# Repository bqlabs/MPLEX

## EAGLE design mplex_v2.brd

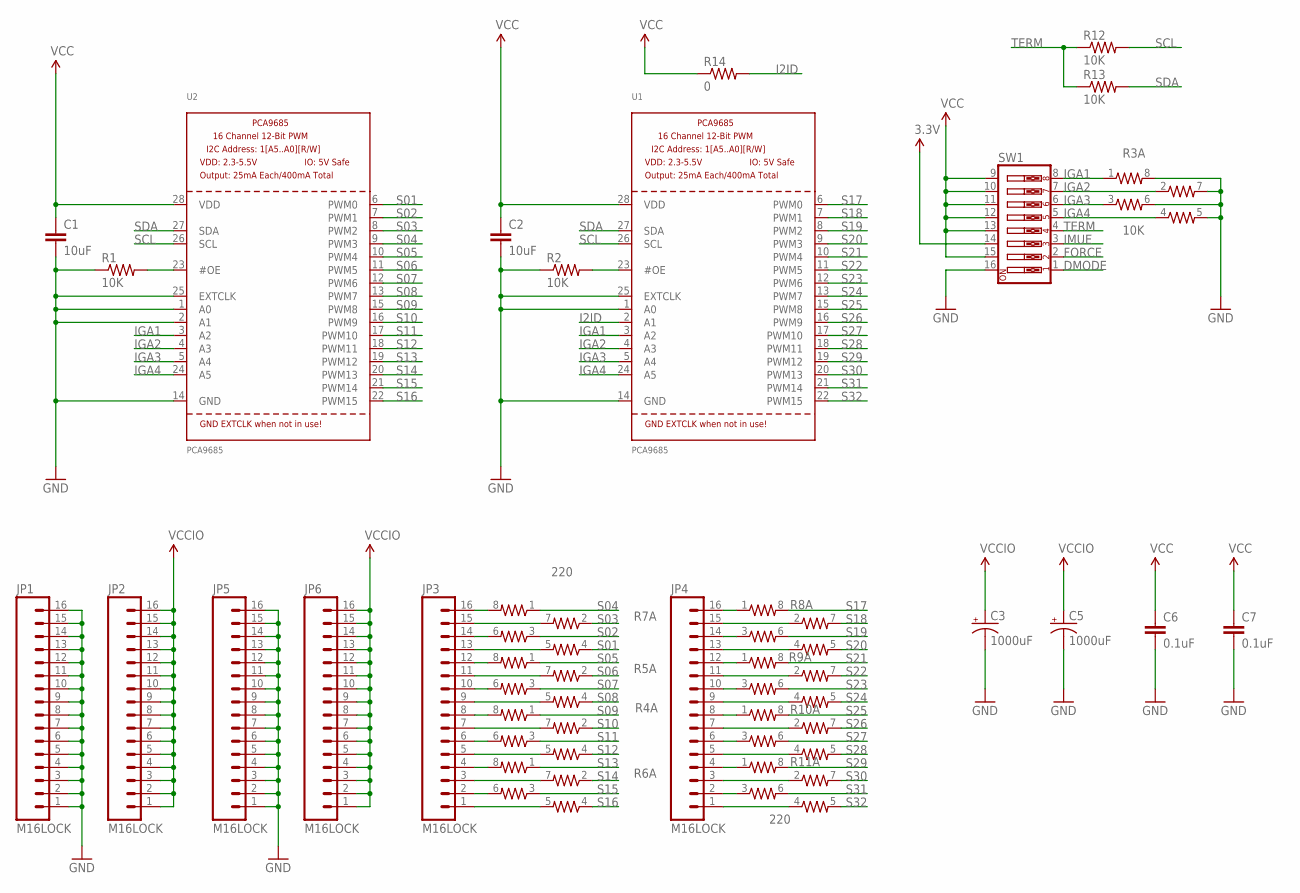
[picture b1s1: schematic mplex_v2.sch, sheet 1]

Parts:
C1, C2: 10uF; 0603-CAP
C3, C5: 1000uF; PANASONIC_D
C6, C7: 0.1uF; 0603-CAP
JP1, JP2, JP3, JP4, JP5, JP6: M16LOCK; 1X16_LOCK
R1, R2, R12, R13: 10K; 0603-RES
R3: 10K; 0603-ARV
R4, R5, R6, R7, R8, R9, R10, R11: 220; 0603-ARV
R14: 0; 0603-RES
SW1: SW_DIP-8-SMT-HALFSIZE; DIPSWITCH-08-50MIL
U1, U2: PCA9685; TSSOP28

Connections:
3.3V: SW1.14; also elsewhere on the board
DMODE: SW1.1; also elsewhere on the board
FORCE: SW1.2; also elsewhere on the board
GND: C1.2, C2.2, C3.-, C5.-, C6.2, C7.2, JP1.1, JP1.2, JP1.3, JP1.4, JP1.5, JP1.6, JP1.7, JP1.8, JP1.9, JP1.10, JP1.11, JP1.12, JP1.13, JP1.14, JP1.15, JP1.16, JP5.1, JP5.2, JP5.3, JP5.4, JP5.5, JP5.6, JP5.7, JP5.8, JP5.9, JP5.10, JP5.11, JP5.12, JP5.13, JP5.14, JP5.15, JP5.16, R1.1, R2.1, R3.5 (2), R3.6 (2), R3.7 (2), R3.8 (2), SW1.16, U1.1 (A0), U1.14 (GND), U1.25 (EXTCLK), U2.1 (A0), U2.2 (A1), U2.14 (GND), U2.25 (EXTCLK); also elsewhere on the board
I2ID: R14.2, U1.2 (A1)
IGA1: R3.1, SW1.8, U1.3 (A2), U2.3 (A2); also elsewhere on the board
IGA2: R3.2 (1), SW1.7, U1.4 (A3), U2.4 (A3); also elsewhere on the board
IGA3: R3.3 (1), SW1.6, U1.5 (A4), U2.5 (A4); also elsewhere on the board
IGA4: R3.4 (1), SW1.5, U1.24 (A5), U2.24 (A5); also elsewhere on the board
IMUE: SW1.3; also elsewhere on the board
unnamed: JP3.16, R7.8 (2)
unnamed: JP3.15, R7.7 (2)
unnamed: R1.2, U2.23 (#OE)
unnamed: R2.2, U1.23 (#OE)
unnamed: JP3.14, R7.6 (2)
unnamed: JP3.13, R7.5 (2)
unnamed: JP3.11, R5.7 (2)
unnamed: JP3.12, R5.8 (2)
unnamed: JP3.10, R5.6 (2)
unnamed: JP3.9, R5.5 (2)
unnamed: JP3.8, R4.8 (2)
unnamed: JP3.7, R4.7 (2)
unnamed: JP3.6, R4.6 (2)
unnamed: JP3.5, R4.5 (2)
unnamed: JP3.4, R6.8 (2)
unnamed: JP3.3, R6.7 (2)
unnamed: JP3.2, R6.6 (2)
unnamed: JP3.1, R6.5 (2)
unnamed: JP4.16, R8.1
unnamed: JP4.15, R8.2 (1)
unnamed: JP4.14, R8.3 (1)
unnamed: JP4.13, R8.4 (1)
unnamed: JP4.12, R9.1
unnamed: JP4.11, R9.2 (1)
unnamed: JP4.10, R9.3 (1)
unnamed: JP4.9, R9.4 (1)
unnamed: JP4.8, R10.1
unnamed: JP4.7, R10.2 (1)
unnamed: JP4.6, R10.3 (1)
unnamed: JP4.5, R10.4 (1)
unnamed: JP4.4, R11.1
unnamed: JP4.3, R11.2 (1)
unnamed: JP4.2, R11.3 (1)
unnamed: JP4.1, R11.4 (1)
S01: R7.4 (1), U2.6 (PWM0)
S02: R7.3 (1), U2.7 (PWM1)
S03: R7.2 (1), U2.8 (PWM2)
S04: R7.1, U2.9 (PWM3)
S05: R5.1, U2.10 (PWM4)
S06: R5.2 (1), U2.11 (PWM5)
S07: R5.3 (1), U2.12 (PWM6)
S08: R5.4 (1), U2.13 (PWM7)
S09: R4.1, U2.15 (PWM8)
S10: R4.2 (1), U2.16 (PWM9)
S11: R4.3 (1), U2.17 (PWM10)
S12: R4.4 (1), U2.18 (PWM11)
S13: R6.1, U2.19 (PWM12)
S14: R6.2 (1), U2.20 (PWM13)
S15: R6.3 (1), U2.21 (PWM14)
S16: R6.4 (1), U2.22 (PWM15)
S17: R8.8 (2), U1.6 (PWM0)
S18: R8.7 (2), U1.7 (PWM1)
S19: R8.6 (2), U1.8 (PWM2)
S20: R8.5 (2), U1.9 (PWM3)
S21: R9.8 (2), U1.10 (PWM4)
S22: R9.7 (2), U1.11 (PWM5)
S23: R9.6 (2), U1.12 (PWM6)
S24: R9.5 (2), U1.13 (PWM7)
S25: R10.8 (2), U1.15 (PWM8)
S26: R10.7 (2), U1.16 (PWM9)
S27: R10.6 (2), U1.17 (PWM10)
S28: R10.5 (2), U1.18 (PWM11)
S29: R11.8 (2), U1.19 (PWM12)
S30: R11.7 (2), U1.20 (PWM13)
S31: R11.6 (2), U1.21 (PWM14)
S32: R11.5 (2), U1.22 (PWM15)
SCL: R12.2, U1.26 (SCL), U2.26 (SCL); also elsewhere on the board
SDA: R13.2, U1.27 (SDA), U2.27 (SDA); also elsewhere on the board
TERM: R12.1, R13.1, SW1.4
VCC: C1.1, C2.1, C6.1, C7.1, R14.1, SW1.9, SW1.10, SW1.11, SW1.12, SW1.13, SW1.15, U1.28 (VDD), U2.28 (VDD); also elsewhere on the board
VCCIO: C3.+, C5.+, JP2.1, JP2.2, JP2.3, JP2.4, JP2.5, JP2.6, JP2.7, JP2.8, JP2.9, JP2.10, JP2.11, JP2.12, JP2.13, JP2.14, JP2.15, JP2.16, JP6.1, JP6.2, JP6.3, JP6.4, JP6.5, JP6.6, JP6.7, JP6.8, JP6.9, JP6.10, JP6.11, JP6.12, JP6.13, JP6.14, JP6.15, JP6.16; also elsewhere on the board

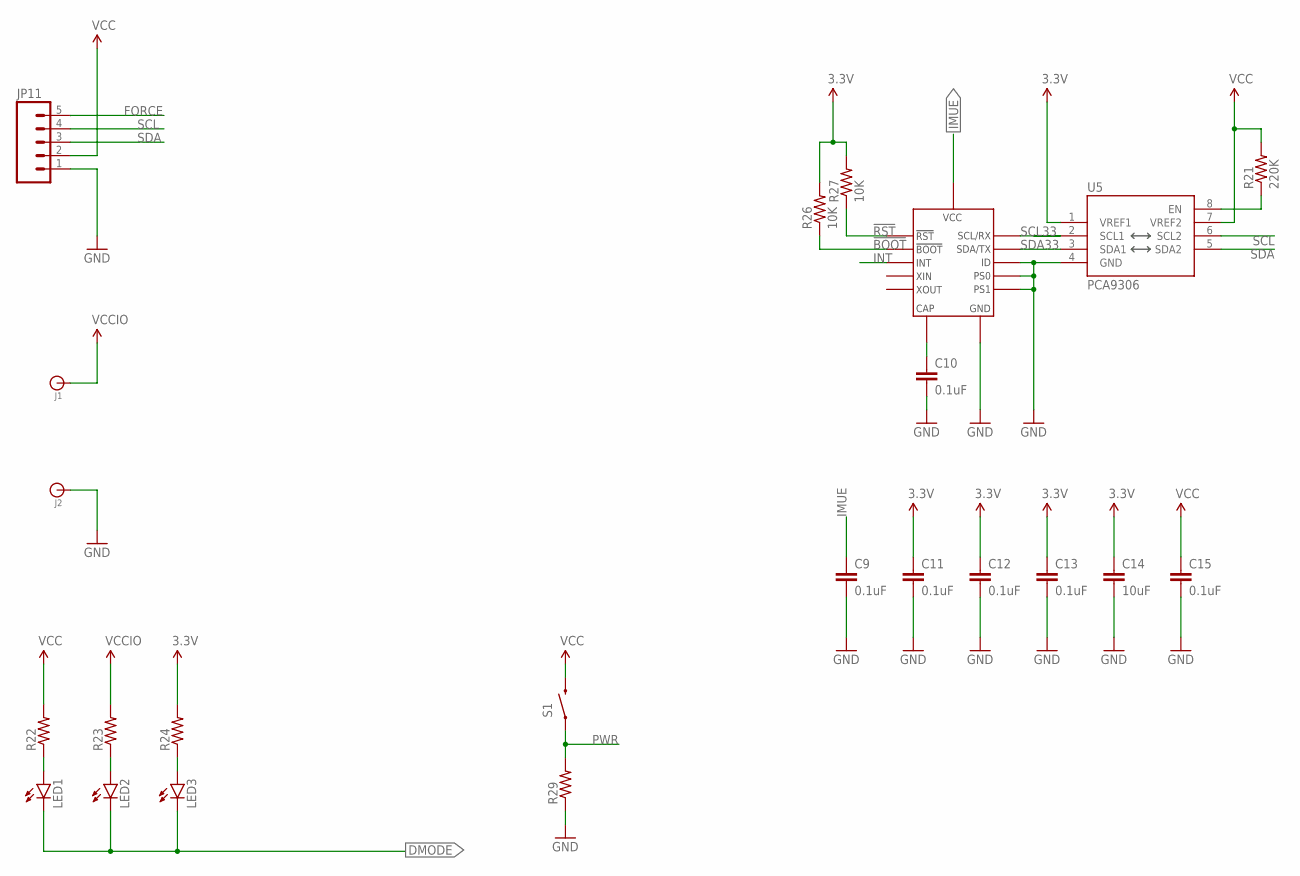
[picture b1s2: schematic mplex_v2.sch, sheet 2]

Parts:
C9, C10, C11, C12, C13, C15: 0.1uF; 0603-CAP
C14: 10uF; 0603-CAP
J1, J2: BANANA_CONN
JP11: M05LOCK; 1X05_LOCK
LED1, LED2, LED3: LED0603; LED-0603
R21: 220K; 0603-RES
R22, R23, R24, R29: RESISTOR0603-RES; 0603-RES
R26, R27: 10K; 0603-RES
S1: SWITCH-MOMENTARY-2SMD; TACTILE-SWITCH-SMD
U4: BNO055
U5: PCA9306; PCA9306DC-1:1

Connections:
3.3V: C11.1, C12.1, C13.1, C14.1, R24.2, R26.2, R27.2, U5.1 (VREF1); also elsewhere on the board
!BOOT: R26.1, U4.4 (BOOT)
!RST: R27.1, U4.1 (RST)
DMODE: LED1.C, LED2.C, LED3.C; also elsewhere on the board
FORCE: JP11.5; also elsewhere on the board
GND: C9.2, C10.2, C11.2, C12.2, C13.2, C14.2, C15.2, J2.P$1, JP11.1, R29.1, U4.2 (GND), U4.5 (PS1), U4.6 (PS0), U4.10 (GND), U4.15 (GND), U4.16 (GND), U4.17 (ID), U4.18 (GND), U4.25 (GND), U5.4 (GND); also elsewhere on the board
IMUE: C9.1, U4.3 (VCC), U4.28 (VCC); also elsewhere on the board
INT: U4.14 (INT)
unnamed: LED1.A, R22.1
unnamed: R21.1, U5.8 (EN)
unnamed: LED2.A, R23.1
unnamed: C10.1, U4.9 (CAP)
unnamed: LED3.A, R24.1
PWR: R29.2, S1.1
SCL: JP11.4, U5.6 (SCL2); also elsewhere on the board
SCL33: U4.19 (SCL/RX), U5.2 (SCL1)
SDA: JP11.3, U5.5 (SDA2); also elsewhere on the board
SDA33: U4.20 (SDA/TX), U5.3 (SDA1)
VCC: C15.1, JP11.2, R21.2, R22.2, S1.3 (2), U5.7 (VREF2); also elsewhere on the board
VCCIO: J1.P$1, R23.2; also elsewhere on the board

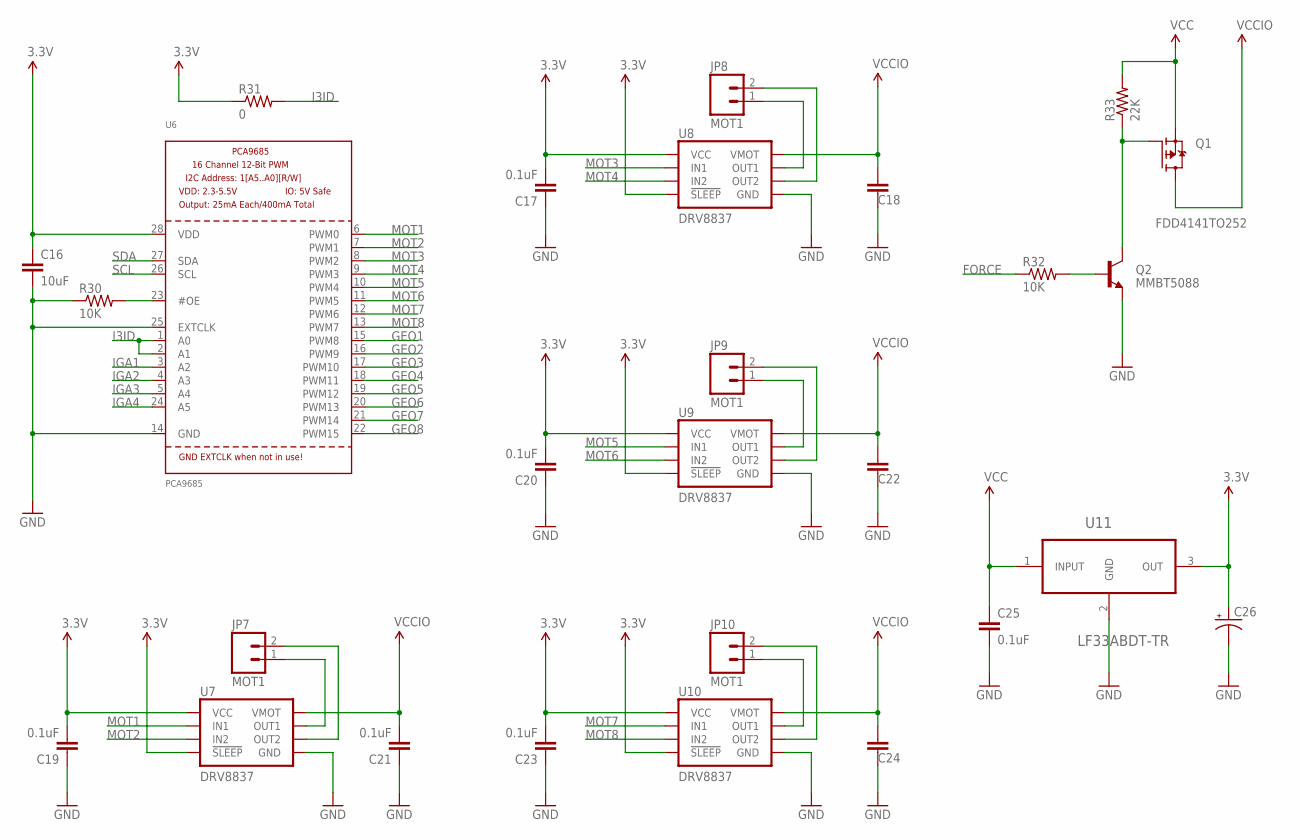
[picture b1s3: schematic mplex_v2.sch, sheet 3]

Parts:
C16: 10uF; 0603-CAP
C17, C18, C19, C20, C21, C22, C23, C24: 0.1uF; 0603-CAP
C25: 0.1uF; 1210
C26: CAP_POLD; PANASONIC_D
JP7, JP8, JP9, JP10: MOT1; MOLEX-1X2
Q1: FDD4141TO252; TO252
Q2: MMBT5088; SOT23-3
R30, R32: 10K; 0603-RES
R31: 0; 0603-RES
R33: 22K; 0603-RES
U6: PCA9685; TSSOP28
U7, U8, U9, U10: DRV8837; DSG
U11: LF33ABDT-TR; TO228P972X240-3N

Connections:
3.3V: C16.1, C17.2, C19.2, C20.2, C23.2, C26.+, R31.1, U6.28 (VDD), U7.7 (!SLEEP), U7.8 (VCC), U8.7 (!SLEEP), U8.8 (VCC), U9.7 (!SLEEP), U9.8 (VCC), U10.7 (!SLEEP), U10.8 (VCC), U11.3 (OUT); also elsewhere on the board
FORCE: R32.1; also elsewhere on the board
GEO1: U6.15 (PWM8)
GEO2: U6.16 (PWM9)
GEO3: U6.17 (PWM10)
GEO4: U6.18 (PWM11)
GEO5: U6.19 (PWM12)
GEO6: U6.20 (PWM13)
GEO7: U6.21 (PWM14)
GEO8: U6.22 (PWM15)
GND: C16.2, C17.1, C18.1, C19.1, C20.1, C21.1, C22.1, C23.1, C24.1, C25.2, C26.-, Q2.2 (E), R30.1, U6.14 (GND), U6.25 (EXTCLK), U7.4 (GND), U7.PAD (GND), U8.4 (GND), U8.PAD (GND), U9.4 (GND), U9.PAD (GND), U10.4 (GND), U10.PAD (GND), U11.2 (GND); also elsewhere on the board
I3ID: R31.2, U6.1 (A0), U6.2 (A1)
IGA1: U6.3 (A2); also elsewhere on the board
IGA2: U6.4 (A3); also elsewhere on the board
IGA3: U6.5 (A4); also elsewhere on the board
IGA4: U6.24 (A5); also elsewhere on the board
MOT1: U6.6 (PWM0), U7.6 (IN1)
MOT2: U6.7 (PWM1), U7.5 (IN2)
MOT3: U6.8 (PWM2), U8.6 (IN1)
MOT4: U6.9 (PWM3), U8.5 (IN2)
MOT5: U6.10 (PWM4), U9.6 (IN1)
MOT6: U6.11 (PWM5), U9.5 (IN2)
MOT7: U6.12 (PWM6), U10.6 (IN1)
MOT8: U6.13 (PWM7), U10.5 (IN2)
unnamed: R30.2, U6.23 (#OE)
unnamed: JP7.1, U7.2 (OUT1)
unnamed: JP7.2, U7.3 (OUT2)
unnamed: JP8.1, U8.2 (OUT1)
unnamed: JP8.2, U8.3 (OUT2)
unnamed: JP9.1, U9.2 (OUT1)
unnamed: JP9.2, U9.3 (OUT2)
unnamed: JP10.1, U10.2 (OUT1)
unnamed: Q2.1 (B), R32.2
unnamed: Q1.1 (G), Q2.3 (C), R33.1
unnamed: JP10.2, U10.3 (OUT2)
SCL: U6.26 (SCL); also elsewhere on the board
SDA: U6.27 (SDA); also elsewhere on the board
VCC: C25.1, Q1.2 (S), R33.2, U11.1 (INPUT); also elsewhere on the board
VCCIO: C18.2, C21.2, C22.2, C24.2, Q1.3 (D), U7.1 (VMOT), U8.1 (VMOT), U9.1 (VMOT), U10.1 (VMOT); also elsewhere on the board

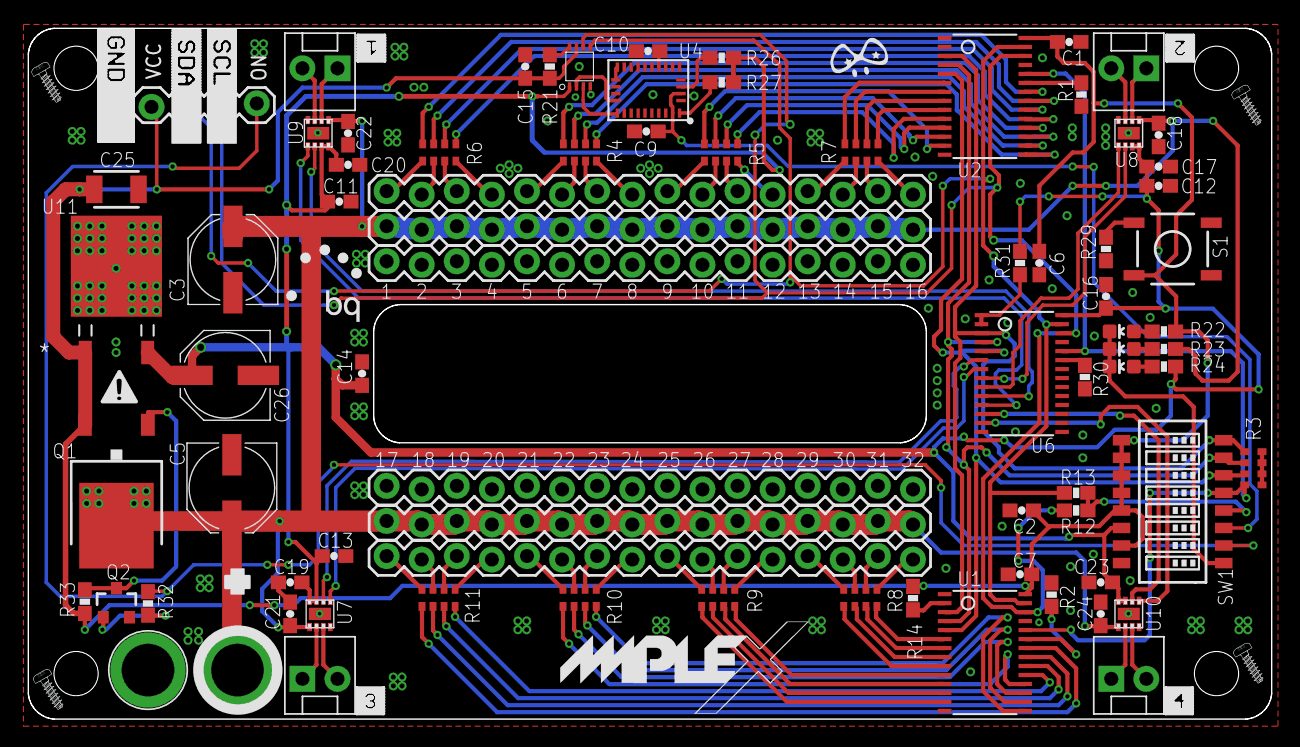
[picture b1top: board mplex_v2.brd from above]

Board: 2 copper layers, 90.0 x 50.0 mm, 94 parts (0 on the bottom side), 111 nets.

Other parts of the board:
U$1, U$3, U$4, U$6: SCREW
U$2: MPLEX_LOGO
U$5: S_1
U$7: S_ATTENTION
U$8: PIGHIXXX_LOGO
U$9: BQ_LOGO_SMALL
U$10: S_2
U$11: S_3
U$12: S_4
U$13: S_SCL
U$14: S_SDA
U$15: S_KICIK_GND_2

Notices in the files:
parts and their libraries:
SparkFun-Capacitors: Licensing: Creative Commons ShareAlike 4.0 International - https://creativecommons.org/licenses/by-sa/4.0
